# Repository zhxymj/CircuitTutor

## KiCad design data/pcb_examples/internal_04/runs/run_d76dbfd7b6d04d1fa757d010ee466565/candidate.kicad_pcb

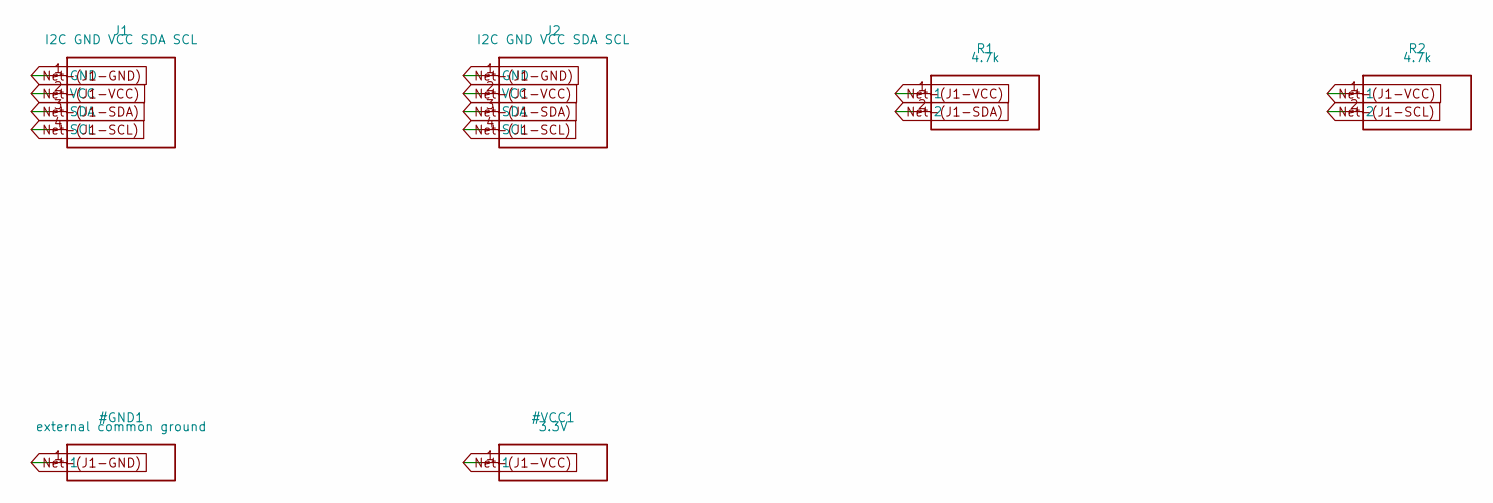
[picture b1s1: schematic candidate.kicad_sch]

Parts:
J1, J2: I2C GND VCC SDA SCL; PinHeader_1x04_P2.54mm_Vertical; MPN TSW-104-07-G-S
R1, R2: 4.7k; R_0805_2012Metric; MPN RC0805FR-074K7L

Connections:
unnamed: J1.1 (GND), J2.1 (GND)
unnamed: J1.4 (SCL), J2.4 (SCL), R2.2
unnamed: J1.3 (SDA), J2.3 (SDA), R1.2
unnamed: J1.2 (VCC), J2.2 (VCC), R1.1, R2.1

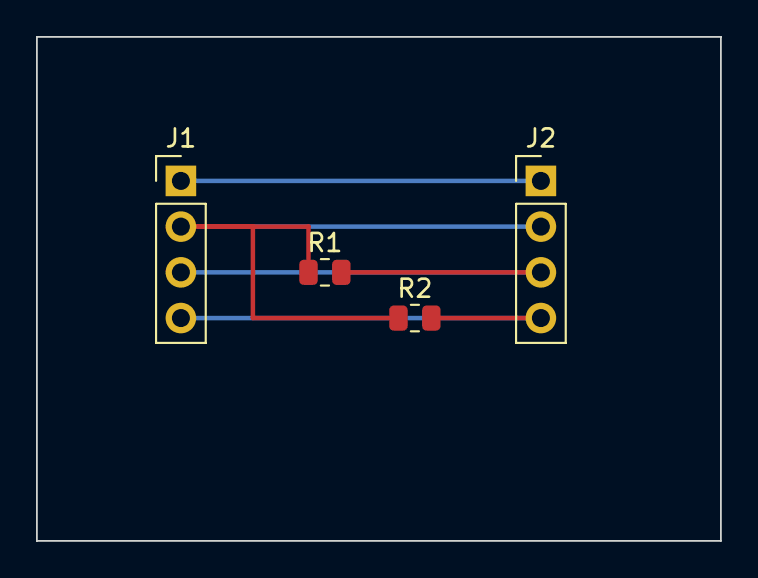
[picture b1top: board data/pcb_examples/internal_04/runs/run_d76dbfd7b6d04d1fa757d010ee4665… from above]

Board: 2 copper layers, 38.0 x 28.0 mm, 4 parts (0 on the bottom side), 4 nets.

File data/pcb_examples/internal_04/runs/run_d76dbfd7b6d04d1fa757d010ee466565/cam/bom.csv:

Reference,Value,MPN,Manufacturer,Footprint,Datasheet
J1,I2C GND VCC SDA SCL,TSW-104-07-G-S,Samtec,Connector_PinHeader_2.54mm:PinHeader_1x04_P2.54mm_Vertical,https://www.samtec.com/products/tsw-104-07-g-s
J2,I2C GND VCC SDA SCL,TSW-104-07-G-S,Samtec,Connector_PinHeader_2.54mm:PinHeader_1x04_P2.54mm_Vertical,https://www.samtec.com/products/tsw-104-07-g-s
R1,4.7k,RC0805FR-074K7L,YAGEO,Resistor_SMD:R_0805_2012Metric,https://www.yageogroup.com/component-documentation/download/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
R2,4.7k,RC0805FR-074K7L,YAGEO,Resistor_SMD:R_0805_2012Metric,https://www.yageogroup.com/component-documentation/download/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

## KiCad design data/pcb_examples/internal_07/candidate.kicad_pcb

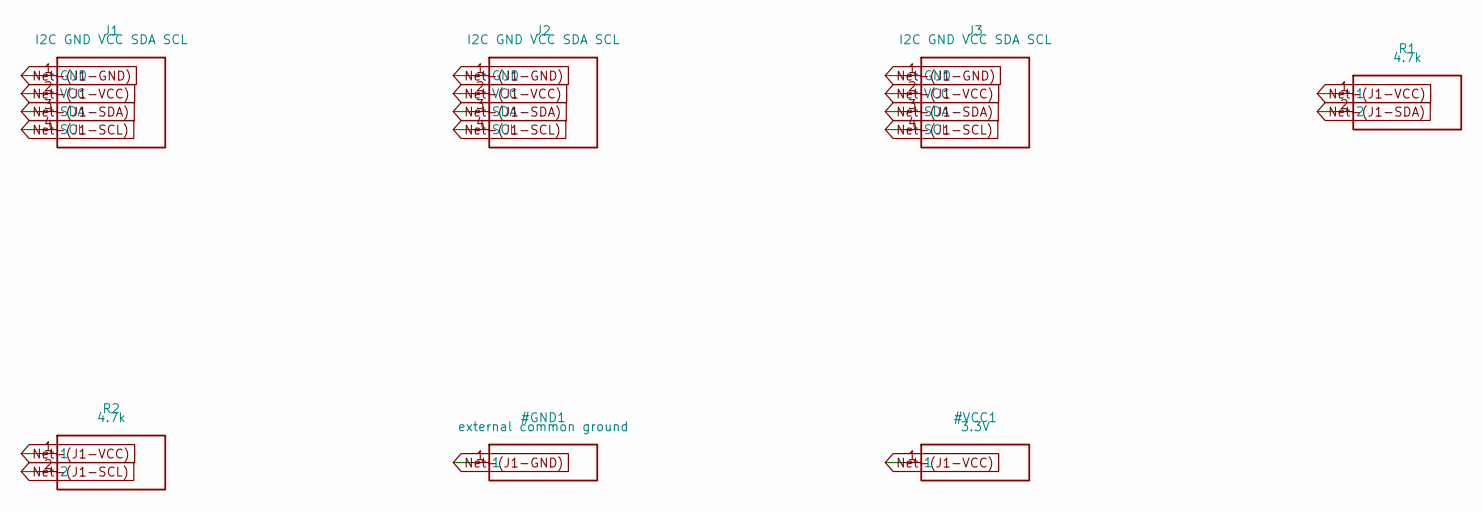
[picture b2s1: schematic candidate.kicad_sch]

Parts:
J1, J2, J3: I2C GND VCC SDA SCL; PinHeader_1x04_P2.54mm_Vertical; MPN TSW-104-07-G-S
R1, R2: 4.7k; R_0805_2012Metric; MPN RC0805FR-074K7L

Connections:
unnamed: J1.1 (GND), J2.1 (GND), J3.1 (GND)
unnamed: J1.4 (SCL), J2.4 (SCL), J3.4 (SCL), R2.2
unnamed: J1.3 (SDA), J2.3 (SDA), J3.3 (SDA), R1.2
unnamed: J1.2 (VCC), J2.2 (VCC), J3.2 (VCC), R1.1, R2.1

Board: 2 copper layers, 5 parts (0 on the bottom side), 4 nets, no tracks yet.
